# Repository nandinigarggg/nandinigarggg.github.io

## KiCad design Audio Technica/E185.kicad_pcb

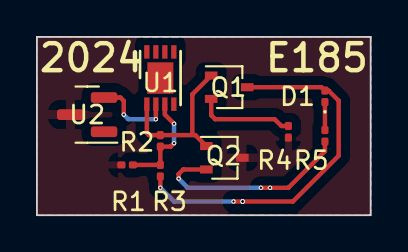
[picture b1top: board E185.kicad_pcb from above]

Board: 2 copper layers, 18.5 x 9.9 mm, 10 parts (0 on the bottom side), 8 nets.

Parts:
D1: LED; LED_0201_0603Metric
Q1: 2SC4213; SOT-323_SC-70
Q2: BC857W; SOT-323_SC-70
R1, R2, R3, R4, R5: R; R_0201_0603Metric
U1: MCP6002-xMC; DFN-8-1EP_3x2mm_P0.5mm_EP1.75x1.45mm
U2: LM35-LP; SOT-23

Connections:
0: Q2.3 (C), R1.2, R4.1, U2.3 (GND)
5V: D1.2 (A), Q1.3 (C), R3.1
unnamed: D1.1 (K), R5.2
unnamed: Q1.1 (B), Q2.1 (B), R2.2, U1.1
unnamed: Q1.2 (E), R4.2
unnamed: Q2.2 (E), R5.1
unnamed: R1.1, R2.1, R3.2, U1.3 (+)
unnamed: U1.2 (-), U2.2 (V_{OUT})

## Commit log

2024-11-18 Updated the gitignore
2024-11-18 Initialising gh-pages branch
2024-11-18 Built site for gh-pages
